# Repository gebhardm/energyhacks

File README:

energyhacks
===========

Some small gadgets providing certain convenience when doing energy metering,
consumption control, etc.

Project structure:
|
|--- AVRNetIOduino: Use the Pollin AVR NetIO board with the Arduino IDE
|
|--- Arduino: Miscellaneous sketches for the Arduino
|
|--- ElektroCamp: Slides of talks held at Elektro Camp events
|
|--- Impulsformer: Convert analog input from a current clamp to S0-impulses/kWh
|
|--- Netfrequency: Show the actual power grid frequency in a range of 50+/-0.2Hz
|
|--- OpticPulseSensor: Use a standard PLL schematics to optically detect pulses
|                      from gas or water meters
|
|--- Rapidbot: Software for the MakeMendel Rapidbot 3D printer V1.0 with
|              Generation6 driver board
|
|--- RaspberryPi: Some programs and scripts for use on a Raspberry Pi
|
|--- RS232-RS485-Converter: Convert legacy serial I/O to RS-485 with flow control 
|
`--- TempGuard: Use temperature sensors to control a warm water circulation pump

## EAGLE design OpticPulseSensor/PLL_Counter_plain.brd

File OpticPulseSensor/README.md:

#Optic Pulse Sensor

Use a NE567 to detect the reading of a reflexive optocoupler and drive the LED of an optocoupler
for galvanic decoupled open-collector output; the plain version is without the extra optocoupler
as the 567 has open collector (OC) output (in this case w/o galvanic decoupling).

Use the trimmer resistor to correctly detect light reflexion.

This schematics is set up corresponding to the many standard layouts to build a light barrier.
The frequency of the 567's oscillator is set to around 4 kHz, enough to prevent stray light
irritations.

Markus Gebhard, February 2013

Under MIT license.

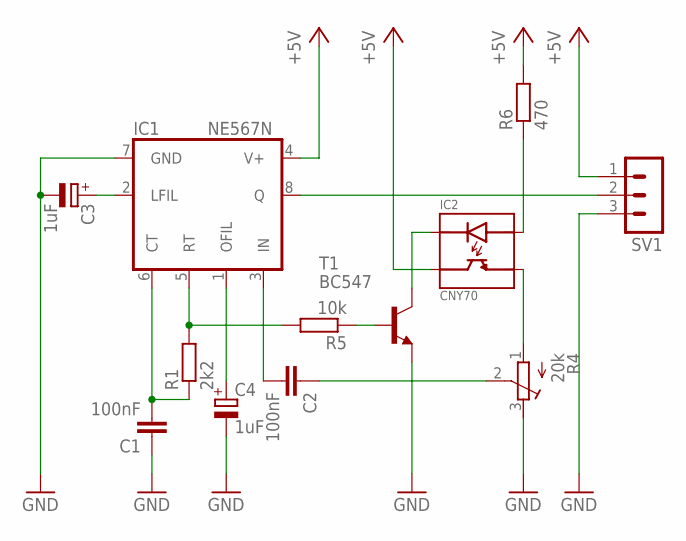
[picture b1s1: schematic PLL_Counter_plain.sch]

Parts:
C1, C2: 100nF; C025-025X050
C3, C4: 1uF; E2,5-5
IC1: NE567N; DIL08
IC2: CNY70
R1: 2k2; 0204/7
R4: 20k; RTRIM64X
R5: 10k; 0204/7
R6: 470; 0204/7
SV1: MA03-1
T1: BC547; TO92

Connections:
+5V: IC1.4 (V+), IC2.DC, R6.2, SV1.1
GND: C1.1, C3.-, C4.-, IC1.7 (GND), R4.3 (E), SV1.3, T1.1 (E)
unnamed: IC2.EK, T1.3 (C)
unnamed: IC1.5 (RT), R1.2, R5.2
unnamed: C1.2, IC1.6 (CT), R1.1
unnamed: IC1.8 (Q), SV1.2
unnamed: C2.2, IC1.3 (IN)
unnamed: IC2.DE, R4.1 (A)
unnamed: R5.1, T1.2 (B)
unnamed: IC2.EA, R6.1
unnamed: C3.+, IC1.2 (LFIL)
unnamed: C4.+, IC1.1 (OFIL)
unnamed: C2.1, R4.2 (S)

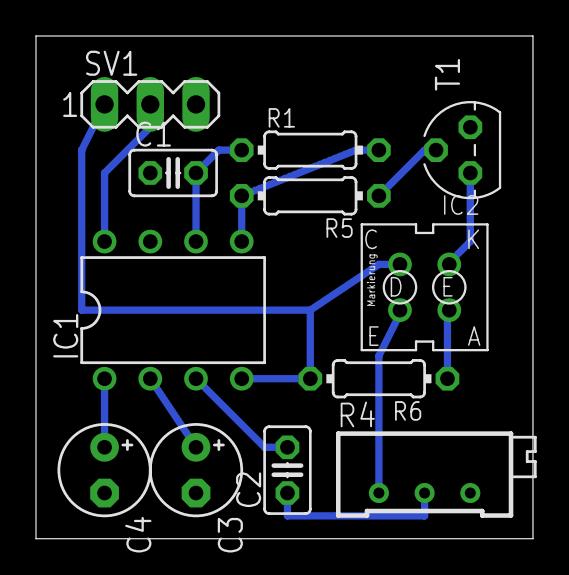
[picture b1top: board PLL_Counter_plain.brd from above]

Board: 2 copper layers, 27.6 x 27.9 mm, 12 parts (0 on the bottom side), 13 nets.

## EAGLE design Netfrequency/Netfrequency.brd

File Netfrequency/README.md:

# Measuring the mains frequency

This device shows with 9 LEDs the current frequency on which the grid
operates.

In Europe the mean grid frequency is 50Hz. Due to increasing
amount of renewable energy put into the grid it is said by the grid
administration "that it is hard to maintain the mean 50Hz". Thus by
too much power in the grid, the frequency rises (see the 50.2Hz problem
in the internet...)

This device - inspired by an Elektor article from January 2012 - allows
to check what is on the grid.
The current code indicates frequencies between 49,8Hz and 50,2Hz...

Have fun.

Markus Gebhard, Jan to July 2012

Needless to say: The grid's voltage may be harmful, so keep your fingers
off this device if you are not sure what you are doing ;-)

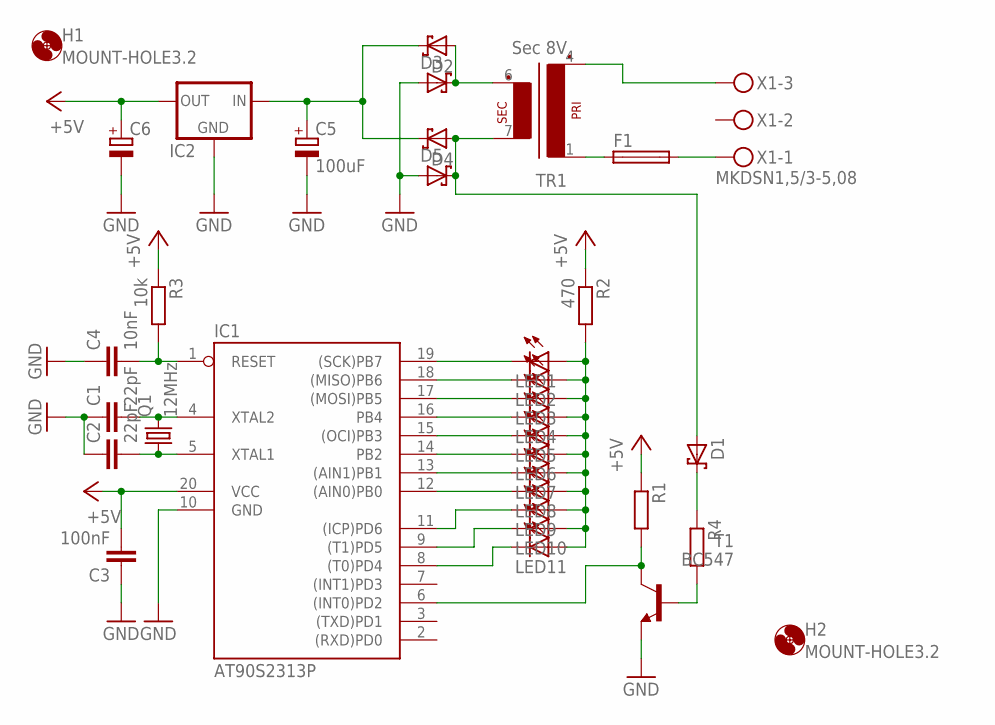
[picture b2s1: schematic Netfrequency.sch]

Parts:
C1, C2: 22pF; C025-025X050
C3: 100nF; C025-025X050
C4: 10nF; C025-025X050
C5: 100uF; E5-8,5
C6: CPOL-EUE2.5-6; E2,5-6
D1, D2, D3, D4, D5: SCHOTTKY-DIODEDO35-7; DO35-7
F1: SH22
H1, H2: MOUNT-HOLE3.2; 3,2
IC1: AT90S2313P; DIL20
IC2: 78LXX
LED1, LED2, LED3, LED4, LED5, LED6, LED7, LED8, LED9, LED10, LED11: LEDSQR2X5; LED2X5
Q1: 12MHz; HC49/S
R1, R4: R-EU_0204/7; 0204/7
R2: 470; 0204/7
R3: 10k; 0204/7
T1: BC547; TO92
TR1: Sec 8V; EE20-1
X1: MKDSN1,5/3-5,08

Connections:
+5V: C3.2, C6.+, IC1.20 (VCC), IC2.OUT, R1.1, R2.1, R3.1
GND: C1.1, C2.1, C3.1, C4.1, C5.-, C6.-, D3.A, D5.A, IC1.10 (GND), IC2.GND, T1.1 (E)
unnamed: IC1.19 ((SCK)PB7), LED1.K (C)
unnamed: IC1.18 ((MISO)PB6), LED2.K (C)
unnamed: IC1.17 ((MOSI)PB5), LED3.K (C)
unnamed: IC1.16 (PB4), LED4.K (C)
unnamed: IC1.15 ((OCI)PB3), LED5.K (C)
unnamed: IC1.14 (PB2), LED6.K (C)
unnamed: IC1.13 ((AIN1)PB1), LED7.K (C)
unnamed: IC1.12 ((AIN0)PB0), LED8.K (C)
unnamed: IC1.11 ((ICP)PD6), LED9.K (C)
unnamed: IC1.9 ((T1)PD5), LED10.K (C)
unnamed: IC1.8 ((T0)PD4), LED11.K (C)
unnamed: LED1.A, LED2.A, LED3.A, LED4.A, LED5.A, LED6.A, LED7.A, LED8.A, LED9.A, LED10.A, LED11.A, R2.2
unnamed: C1.2, IC1.4 (XTAL2), Q1.2
unnamed: C2.2, IC1.5 (XTAL1), Q1.1
unnamed: C4.2, IC1.1 (RESET), R3.2
unnamed: IC1.6 ((INT0)PD2), R1.2, T1.3 (C)
unnamed: D2.A, D3.C, TR1.6 (S3)
unnamed: C5.+, D2.C, D4.C, IC2.IN
unnamed: F1.1, TR1.1
unnamed: F1.2, X1.1
unnamed: TR1.4 (P2), X1.3
unnamed: R4.2, T1.2 (B)
unnamed: D1.C, R4.1
unnamed: D1.A, D4.A, D5.C, TR1.7 (S4)

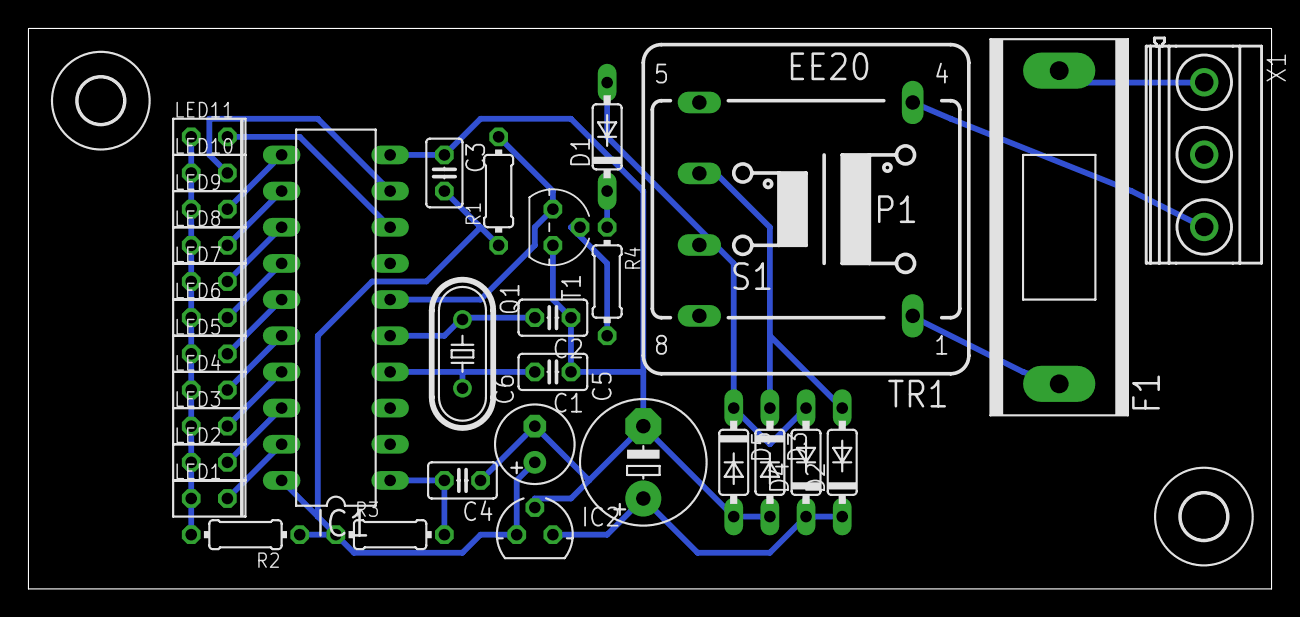
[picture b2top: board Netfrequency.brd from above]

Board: 2 copper layers, 87.3 x 39.4 mm, 35 parts (0 on the bottom side), 26 nets.

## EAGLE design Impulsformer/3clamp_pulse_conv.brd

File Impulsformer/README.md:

# Impulsformer
"Impulsformer" provides a little converter that transforms the current
measured by one respective three current clamp(s) (as used by the 
Fluksometer - see [flukso.net](www.flukso.net)) to an S0-compliant impulse set, 
in the example case 1000 impulses per measured kWh.

The basic use of the converter is for the Fluksometer to enhance it
by one (or three or more, as the used microcontroller's ADCs are not
fully utilized) analog input(s).

The given schematics, board and corresponding software are based on an
Atmel ATtiny13(A) and just a few external components.

The used voltage converter is a low drop variant capable to be "clamped"
to the existing Fluksometer's AC/DC module, so not requiring an
additional voltage source.

The microcontroller may be driven also with lower Vcc and different
operating frequency; the given outline of the one clamp variant is working fine...

Markus Gebhard, Karlsruhe, Germany, April/May 2012

Greetings to the participants of the electrocamp ec1205 held May 4th/5th in Offenburg.
It has been a pleasure taking part...

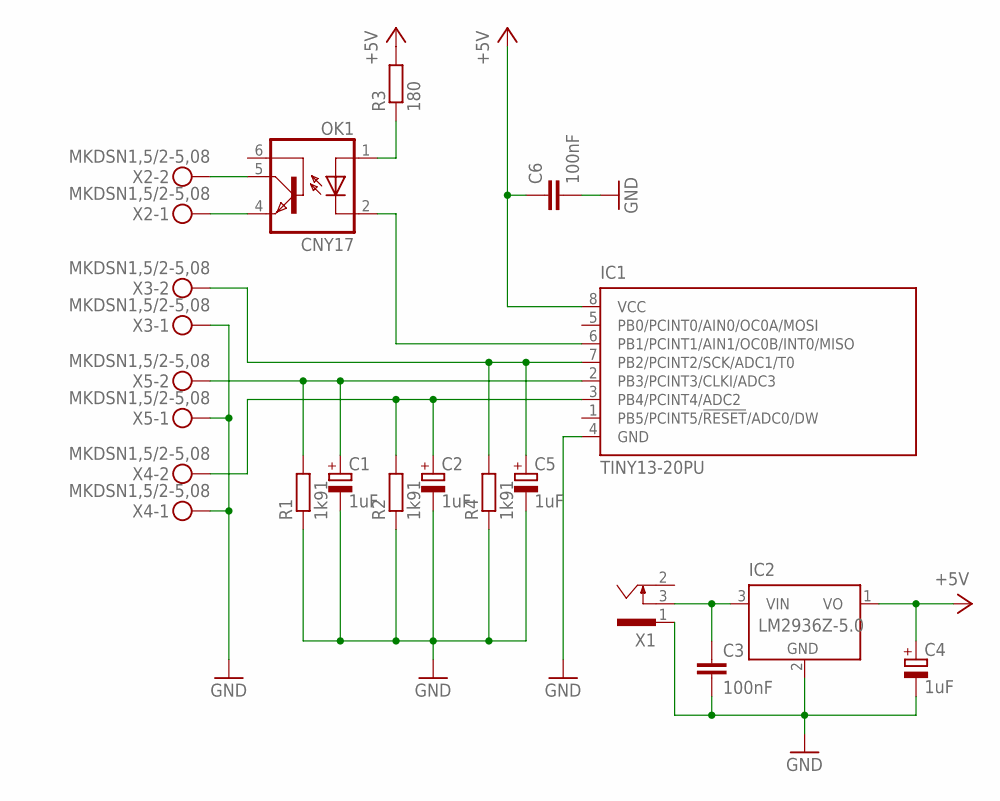
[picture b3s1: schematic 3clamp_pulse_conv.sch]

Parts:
C1, C2, C4, C5: 1uF; E2,5-5
C3, C6: 100nF; C025-025X050
IC1: TINY13-20PU; DIL08
IC2: LM2936Z-5.0; TO92
OK1: CNY17; DIL06
R1, R2, R4: 1k91; 0204/7
R3: 180; 0204/7
X1: SCD-014A; SCD-014-A
X2, X3, X4, X5: MKDSN1,5/2-5,08

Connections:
+5V: C4.+, C6.1, IC1.8 (VCC), IC2.1 (VO), R3.2
GND: C1.-, C2.-, C3.2, C4.-, C5.-, C6.2, IC1.4 (GND), IC2.2 (GND), R1.1, R2.1, R4.1, X1.1, X3.1, X4.1, X5.1
unnamed: C3.1, IC2.3 (VIN), X1.3
unnamed: C1.+, IC1.2 (PB3/PCINT3/CLKI/ADC3), R1.2, X5.2
unnamed: C2.+, IC1.3 (PB4/PCINT4/ADC2), R2.2, X4.2
unnamed: C5.+, IC1.7 (PB2/PCINT2/SCK/ADC1/T0), R4.2, X3.2
unnamed: OK1.1 (A), R3.1
unnamed: IC1.6 (PB1/PCINT1/AIN1/OC0B/INT0/MISO), OK1.2 (C)
unnamed: OK1.5 (COL), X2.2
unnamed: OK1.4 (EMI), X2.1

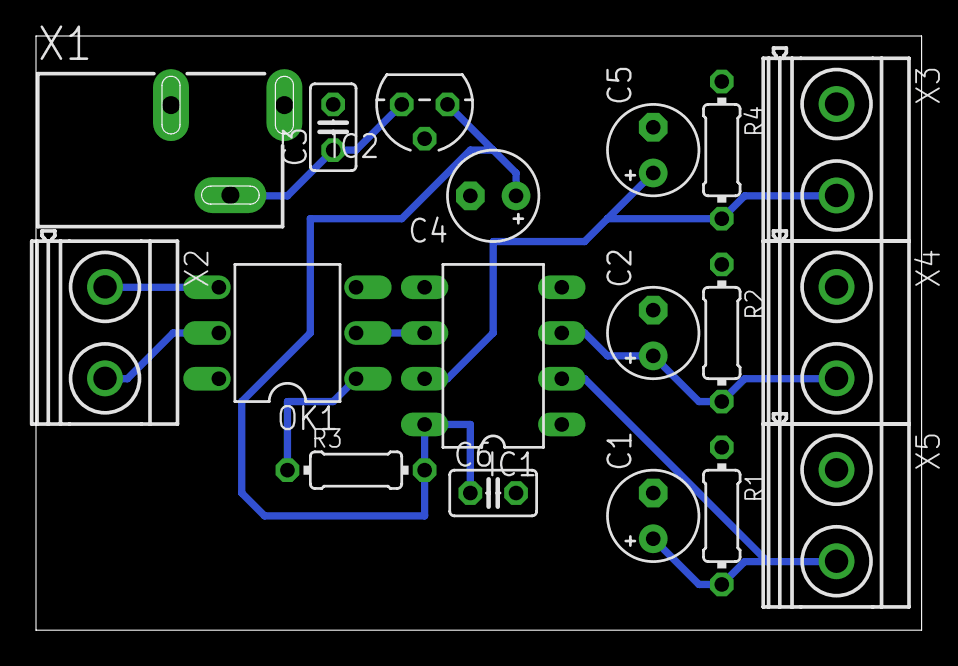
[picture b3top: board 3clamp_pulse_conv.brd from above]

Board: 2 copper layers, 49.2 x 33.0 mm, 18 parts (0 on the bottom side), 10 nets.

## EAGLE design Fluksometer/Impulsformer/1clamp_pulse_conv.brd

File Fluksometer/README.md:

# Fluksometer Additions

This folder contains stuff I made during my times of operating a
Fluksometer (FLM), a neat little appliance to do energy metering and display.

Refer to https://www.flukso.net/ for more details; the project seems abandoned.

As I also moved out of an environment where I could use the FLM "on premise",
this folder's content is mainly for the records and whomever wants to catch
up with some ideas spread in the respective community "that time".

* [FakeSensor](FakeSensor) - A simple fake sensor provider to test an MQTT broker
* [Flukso](Flukso) - Tips and tricks with respect to the flukso.net Fluksometer
* [Gauge](Gauge) - A simple Justgage gauge visualizing values received from MQTT topics
* [Graph](Graph) - A simple Flot graph visualizing values received from MQTT topics
* [Impulsformer](Impulsformer) - Convert analog input from a current clamp to S0-impulses/kWh
* [MQTTRealtime](MQTTRealtime) - A simple Chart graph visualizing values of an FLM03
* [OpticPulseSensor](OpticPulseSensor) - Use a standard PLL schematics to optically detect pulses from gas or water meters
* [RaspberryPi](RaspberryPi) - Some programs and scripts for use on a Raspberry Pi

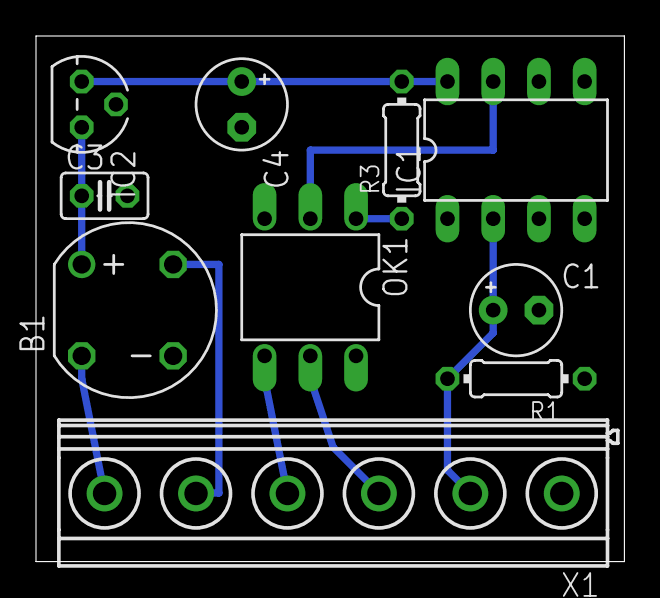
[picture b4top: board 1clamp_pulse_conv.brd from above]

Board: 2 copper layers, 32.7 x 29.2 mm, 10 parts (0 on the bottom side), 10 nets.

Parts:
B1: RB1A
C1: 1uF; E2,5-5
C3: 100nF; C025-025X050
C4: 10uF; E2,5-5
IC1: TINY13-20PU; DIL08
IC2: LM2936Z-5.0; TO92
OK1: CNY17; DIL06
R1: 1k91; 0204/7
R3: 150; 0204/7
X1: MKDSN1,5/6-5,08

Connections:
+5V: C4.+, IC1.8, IC2.1, R3.2
GND: B1.-, C1.-, C3.2, C4.-, IC1.4, IC2.2, R1.1, X1.1
unnamed: B1.+, C3.1, IC2.3
unnamed: C1.+, IC1.2, R1.2, X1.2
unnamed: IC1.7, OK1.2
unnamed: OK1.1, R3.1
unnamed: OK1.5, X1.3
unnamed: OK1.4, X1.4
unnamed: B1.AC2, X1.6
unnamed: B1.AC1, X1.5

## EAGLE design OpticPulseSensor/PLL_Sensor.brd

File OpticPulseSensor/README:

Optic Pulse Sensor

Use a NE567 to detect the reading of a reflexive optocoupler and drive the LED of an optocoupler
for galvanic decoupled open-collector output; the plain version is without the extra optocoupler
as the 567 has OC output (in this case w/o galvanic decoupling).

Use the trimmer resistor to correctly detect light reflexion.

This schematics is set up corresponding to the many standard layouts to build a light barrier.
The frequency of the 567's oscillator is set to around 4 kHz, enough to prevent stray light
irritations.

Markus Gebhard, February 2013

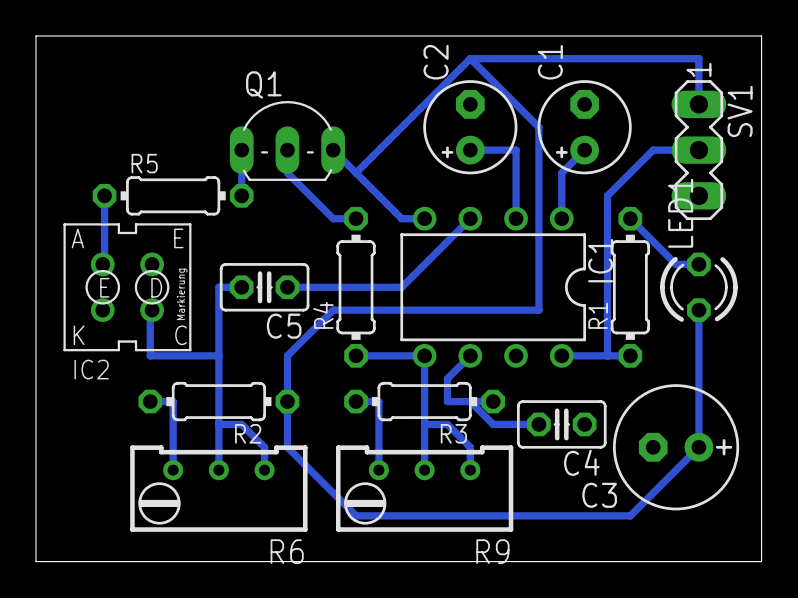
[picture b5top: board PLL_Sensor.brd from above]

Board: 2 copper layers, 40.3 x 29.2 mm, 17 parts (0 on the bottom side), 15 nets.

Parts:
C1, C2: 1uF; E2,5-5
C3: 100uF; E2,5-7
C4: 33nF; C025-025X050
C5: 100nF; C025-025X050
IC1: LM567N; DIL08
IC2: CNY70
LED1: LED3MM
Q1: BC558B; TO92-EBC
R1: 1k; 0204/7
R2, R3: 4k7; 0204/7
R4, R5: 0204/7
R6, R9: 10k; RTRIM64W
SV1: MA03-1

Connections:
+5V: C3.+, IC1.4, LED1.A, Q1.E, R2.1, SV1.1
GND: C1.-, C2.-, C3.-, C4.1, IC1.7, IC2.DE, IC2.EK, SV1.3
unnamed: IC1.8, R1.1, SV1.2
unnamed: LED1.K, R1.2
unnamed: C2.+, IC1.2
unnamed: C1.+, IC1.1
unnamed: C5.1, IC1.3
unnamed: C5.2, IC2.DC, R6.1, R6.2
unnamed: Q1.C, R5.2
unnamed: R2.2, R6.3
unnamed: IC2.EA, R5.1
unnamed: Q1.B, R4.2
unnamed: IC1.5, R4.1, R9.1, R9.2
unnamed: R3.2, R9.3
unnamed: C4.2, IC1.6, R3.1

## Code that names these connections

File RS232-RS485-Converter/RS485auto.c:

/**********************************************************************
Use an ATtiny 13 to drive the write enable pin of a MAX485 to pass
RS-232 characters for the time of a character write

Used to test the RS-485 interface of an SMA DC converter

Markus Gebhard, Karlsruhe, Copyright 2009

This program is free software: you can redistribute it and/or modify
it under the terms of the GNU General Public License as published by
the Free Software Foundation, either version 3 of the License, or
(at your option) any later version.

This program is distributed in the hope that it will be useful,
but WITHOUT ANY WARRANTY; without even the implied warranty of
MERCHANTABILITY or FITNESS FOR A PARTICULAR PURPOSE.  See the
GNU General Public License for more details.

You should have received a copy of the GNU General Public License
along with this program.  If not, see <http://www.gnu.org/licenses/>.
**********************************************************************/

#include <avr/io.h>
#include <avr/interrupt.h>
#include <util/delay.h>

int main()
{
	unsigned char jmprs = 0;
	// init ATtiny13
	// PB0 - RSwrite Output
	// PB1/INT0 - Activity on RS232-TxD-line
	// PB2, 3, 4 - Jumper for Baudrate
	// PB5 unused due to being reset line
	// set PB0 output, all others input
	DDRB |= (1<<PB0);
	// internal Pullup resistors on
	PORTB |= (1<<PB1)|(1<<PB2)|(1<<PB3)|(1<<PB4);
	// /RE on MAX485 to low => read
	PORTB &= ~(1<<PB0);
	// read jumpers for baud setting
	jmprs |= (PINB>>2)&7;
	// main loop to react on RS-232 write
	while (1)
	{
		if (!(PINB&(1<<PB1)))
		{
			PORTB |= (1<<PB0);
			// delay until a character is sent - with some correction
			if 		(jmprs==7)	_delay_us(86);		// 115k2 baud
			else if (jmprs==6)	_delay_us(173-1);	// 57k6
			else if (jmprs==5)	_delay_us(260-2);	// 38k4
			else if (jmprs==4)	_delay_us(520-2);	// 19k2
			else if (jmprs==3)	_delay_us(1041-3);	// 9k6
			else if (jmprs==2)	_delay_us(2083-3);	// 4k8
			else if (jmprs==1)	_delay_us(4166-4);	// 2k4
			else 				_delay_us(8333-5);	// 1k2
			PORTB &= ~(1<<PB0);
		}
	}
	// und tschüß...
	return (0);
}

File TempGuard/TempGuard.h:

/* TempGuard.h version 4.0 */

#include <avr/io.h>
#include <avr/interrupt.h>
#include <util/delay.h>

#define SW_DDR DDRB				// direction of switch port
#define SW_PORT PORTB			// port of switches
#define SW_PIN PINB				// read set switches
#define PUMP PB1				// pin of pump switch

#define BUT_DDR	DDRB			// direction of button port
#define BUT_PORT PORTB			// port of buttons
#define BUT_PIN PINB			// read buttons
#define PLUS PB5				// (+)-button
#define ENTER PB4				// enter button
#define MINUS PB3				// (-)-button

#define RUNTIME 300				// maximum runtime of pump in seconds
#define DT_ON 10				// pump on at 10 Kelvin difference
#define DT_OFF 5				// pump off at 5 Kelvin difference
#define DT_MAX 10				// difference to maximum temperature at pump off
#define WW_MIN 40				// minimal temperature of warm water to start
#define CI_MAX 30				// maximum temperature of circulation
#define T_DOWN 15				// temperature lower limit
#define T_UP 95					// temperature upper limit
#define TCLOCK 206				// Timer start 50Hz: Second >> 256-50
#define SMPL 5					// Sampling all SMPL seconds

#define LCD_DDR	DDRD			// direction of LCD port
#define LCD_PORT PORTD			// port of LCD
#define LCD_PIN PIND			// read LCD port
#define LCD_CLK PD6				// clock-pin of shift register
#define LCD_DATA PD5			// data-pin of shift register
#define LCD_LIGHT PD7			// background light
#define RS_CMD 0				// send command to LCD
#define RS_DATA 1				// send data to LCD
#define LIGHT 60				// time background light on
// Menu definition
#define MENU_TEMP 1
#define MENU_DTON 2
#define MENU_DTOFF 3
//#define MENU_CLOCK 4
#define MENU_CMAX 4
#define MENU_CMIN 5
#define MENU_RESET 6
#define MENU_TMAX 7
//#define MENU_DTMAX 9
#define MENU_MAN 8				// number of menus; last one is always "manual control"

volatile unsigned char SampleCnt;		// counter to next sampling
volatile int T_Ww, T_Ci;				// measured temperatures of warm water and circulation
volatile int T_max;						// measured maximum temperature
volatile int T_last;					// last measured temperature
volatile int dT_on = DT_ON;				// DeltaTemp of pump on
volatile int dT_off = DT_OFF;			// DeltaTemp of pump off
volatile int dT_max = DT_MAX;			// DeltaTemp to MaxTemp of pump off
volatile int T_Ci_max = CI_MAX;			// maximum temperature of circulation
volatile int T_Ww_min = WW_MIN;			// minimum temperature of circulation
volatile unsigned int Rnt = 0;			// runtime of pump
volatile unsigned int t_run = RUNTIME;  // maximum runtime of pump
volatile unsigned char Bkl = 0;			// runtime background light
volatile struct time_struct {
	unsigned char Hrs:5;
	unsigned char Min:6;
	unsigned char Sec:6;
} Time;

volatile unsigned char Hrs, Min, Sec, Day, Mnt, Yr, Menu;

void init_ADC( void );
int read_ADC( unsigned char );
void init_switch( void );
void init_button( void );
void init_TIMER( void );
void Switch_pump( char );
void Switch_light( char );
void User( void );
void Control_pump( void );

void LCD_clock( void );
void LCD_write_nibble(unsigned char, unsigned char );
void LCD_write(unsigned char, unsigned char );
void LCD_clear( void );
void LCD_home( void );
void LCD_init( void );
void LCD_text( char* );
void LCD_pos( unsigned char, unsigned char );
void LCD_int( int );

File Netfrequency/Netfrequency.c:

/* Application to display the net frequency with 9 LEDs
on a ATtiny2313 running at 12MHz
(instead of an AT89C2051P as in German Elektor 01-2012,
pages 22 and following)
INT0 is used to couple the net frequency
LEDs on PORTB: PB7-0 and PORTD: PD6
red:  PB7
yellow: PB6,5
green: PB4,3,2
yellow: PB1,0
red:  PD6

This program is free software: you can redistribute it and/or modify
it under the terms of the GNU General Public License as published by
the Free Software Foundation, either version 3 of the License, or
(at your option) any later version.

This program is distributed in the hope that it will be useful,
but WITHOUT ANY WARRANTY; without even the implied warranty of
MERCHANTABILITY or FITNESS FOR A PARTICULAR PURPOSE.  See the
GNU General Public License for more details.

You should have received a copy of the GNU General Public License
along with this program.  If not, see <http://www.gnu.org/licenses/>.
*/
/***************************************************************************/
//used standard includes 
#include <stdlib.h>
#include <avr/io.h>
#include <avr/interrupt.h>
#include <util/delay.h>
/***************************************************************************/
#define AVG	  				// measure frequency with average calculation
//#define RS232
#ifdef RS232
#define BAUD 19200              // RS232 speed for debugging purposes
#endif
#define NET 50					// set Net default frequency
#define DIVIDER 8				// Prescaler of Timers
#define NETCNT (unsigned int) (F_CPU / DIVIDER / NET) // relevant count takts per Hz
#define DELTA 30				// delta counts per LED
// define the LEDs display frequencies
// example for 50Hz as in Europe:
// Factor = 12.000.000 / 8 / 50 = 30.000 counts equal 50 Hz
// Limits in Europe are 50,2 Hz and 49,8Hz
// 50,2Hz equal 30.120 counts, 49,8Hz equal 29.880 counts
// distributed on 9 LEDs with 50Hz in the center give a delta per LED of 30 counts
/***************************************************************************/
//Header Definition of used  routines (I don't like header files :-))
#ifdef RS232
void init_USART( unsigned int );
void send_USART( unsigned char );
void sendchars_USART( char* );
void send_uint( unsigned int );
#endif
void LED_init( void );
void LED_set( unsigned char );
void LED_clr( unsigned char );
void LED_off( void );
void LED_toggle( unsigned char );
/***************************************************************************/
//Global variables for Interrupt computation
volatile unsigned char lastLED = 0;
volatile unsigned long sum = 0;
volatile unsigned char cnt = 0;
/***************************************************************************/
//Interrupt Routines for computing INT0
ISR(INT0_vect)
{
	int led, timer, t_Hz;
	timer = TCNT1;
	TCNT1 = 0;
	t_Hz = F_CPU / DIVIDER / timer;
	// use timer value only if variance not too large (there are false counts)
	if (abs(NET-t_Hz)<5)
	{
		// measure with average calculation over last second
#ifdef AVG
		sum += timer;
		cnt++;
		if (cnt == NET)
		{
			// the average
			sum /= NET;
			// mapped onto the LEDs
			led = sum;
			led -= NETCNT;
			led /= DELTA;
			led += 5;
			LED_clr(lastLED);
			LED_set(led);
			lastLED = led;
			sum = 0;
			cnt = 0;
		}
#else
		// output measured value directly
		led = timer;
		led -= NETCNT;
		led /= DELTA;
		led += 5;
		LED_clr(lastLED);
		LED_set(led);
		lastLED = led;
#endif
	}
}
/* check, if Timer overflows
ISR(TIMER1_OVF_vect)
{
	TCNT1 = 0;
} */
/***************************************************************************/
#ifdef RS232
//RS-232 Routines
void init_USART( unsigned int bps )
{
	unsigned int baud;
	baud = ( F_CPU / 16UL / bps ) - 1;       // compute Teiler
	UBRRH = (unsigned char) (baud>>8);       // set Baudrate
	UBRRL = (unsigned char) baud;
	UCSRB = (1<<RXEN)|(1<<TXEN);             // RS232-Rx/Tx on
	UCSRC = (3<<UCSZ0);                      // set Protocol 8N1
}

void send_USART( unsigned char c )
{
	while ( !( UCSRA & (1<<UDRE)) );  // wait until transfer buffer empty
	UDR = c;                          // write char
}

void sendchars_USART( char *s )
{
	while ((*s != 0))
	{                                 // output all chars
		send_USART(*s++);
	} 
}

void send_uint( unsigned int n )
{
	unsigned char dig[5], num = 0, i; // compute 5 digit integer without sign
	do
	{
		dig[num++] = ( n % 10 ) + 0x30;
		n /= 10;
	} while (n != 0);
	for (i=num; i!=0; i--) send_USART(dig[i-1]);
}
#endif
/***************************************************************************/
// LED Routines
void LED_init( void )
{
	DDRB = 0xff;
	DDRD = (1<<PD6);
	PORTB = 0xff;
	PORTD = (1<<PD6);
}
// LED on
void LED_set( unsigned char n )
{
	if ((n>0) && (n<9)) PORTB &= ~(1<<(8-n));
	else if (n==9) PORTD &= ~(1<<PD6);
}
// LED off
void LED_clr( unsigned char n )
{
	if ((n>0)&&(n<9)) PORTB |= (1<<(8-n));
	else if (n==9) PORTD |= (1<<PD6);
}
void LED_off( void )
{
	PORTB = 0xff; PORTD = (1<<PD6);
}
void LED_toggle( unsigned char n )
{
	if (n<9) PORTB ^= (1<<(8-n));
	else if (n==9) PORTD ^= (1<<PD6);
}
/***************************************************************************/
// main program
int main( void )
{
	unsigned char i; 		     // counter variable
	// Ausgabe vorbereiten
#ifdef RS232
	init_USART( BAUD );
	send_USART(27); sendchars_USART("[2J"); // clear screen
	sendchars_USART("Net loupe");
#endif
	// Net frequency read preparation
	//MCUCR |= (0x02 << ISC00);  // Interrupt on falling edge of INT0
	MCUCR |= (0x03 << ISC00);  // Interrupt on rising edge on INT0
	GIMSK |= (1 << INT0);   	 // release INT0
	// Timer initialization
	switch (DIVIDER)
	{
	case 1: TCCR1B |= (0x01 << CS10); break; 
	case 8: TCCR1B |= (0x02 << CS10); break; 
	case 64: TCCR1B |= (0x03 << CS10); break;
	}
	//TIMSK  |= (1 << TOIE1);  // Interrupt on timer overflow
	// LEDs initialization
	LED_init();
	// LEDs count through (used just as a appetizer)
	for (i=1;i<=9;i++)
	{
		LED_set(i);
		_delay_ms(250);
		LED_clr(i);
	}
	// Frequency measuring preparation
	sei();                    // activate Interrupt control
	TCNT1 = 0;         		// Timer start
	// program main loop - everything is done in the interrupt
	while (1)
	{
	}
	return(0);
}

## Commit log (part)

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2012-04-20 Initial commit of the source code, schematics and board layout of an analog current clamp to S0 converter. Idea is to add "at least" two more analog channels to the Fluksometer by converting analog t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
2012-04-27 Adding a brief description of the hack
2012-04-28 Add temperature control project
2012-05-06 Adapted code and schema to 1 and 3 clamp variants
2012-05-06 Readme update
2012-05-06 Use plain text for README
2012-05-12 Corrections (result of thinking w/o compiling)
2012-05-13 RS485/RS232 Converter added
2012-05-13 RS485/RS232 jpg and README upd
2012-05-17 Moved to interrupt due timing issues
2012-05-18 Timing is strange...
2012-07-01 Small correction of modulo calculation
2012-07-08 Netfrequency observer added
2012-08-20 Simplicity is not always obvious...
2012-08-21 timing adaptation
2012-08-25 filtering timer measurements
2012-11-11 Start to use Pollin AVR NetIO with Arduino
2012-11-12 Added AVR NetIO Arduino bootloader for ATmega32
2012-11-15 Working Arduino bootloaders for AVR NetIO w/ ATmega644P and 32
2012-11-16 Description update
2012-11-19 Preparation for correct AVRNetIOduino hardware files
2012-11-19 Correct description
2012-12-15 Bootloader LED on prog select jumper
2013-01-12 AVRNetIO minimal server running
2013-01-13 AVRNetIO working with mega32 and mega644p
2013-02-03 TempGuard on Arduino
2013-02-03 TempGuard simple Web display
2013-02-23 Optical Sensor added
2013-02-23 readme upd
2013-02-28 Optoreader with accuracy trimming
2013-03-17 AVRNetIOduino revisited
2013-04-21 ElektroCamp slides
2013-04-21 ReadMe updates
2013-04-26 elektro:camp slides revised
2013-05-11 read Fluksometer with Raspberry Pi
2013-05-11 FLM sensor reader corrected
2013-05-11 readme files updated
2013-05-12 Sensor ID from GUID to str
2013-05-13 logging added
2013-05-13 error handling cont'd
2013-05-14 error enumeration!
2013-05-14 bracket or no bracket, that is the question
2013-05-15 error handling update
2013-05-16 version for mid-time test
2013-05-17 testing and error correction, next round
2013-05-19 small adjustment
2013-05-23 job end handler added
2013-05-24 something learned:funcdef before call
2013-05-30 some more error handling
2013-06-02 first experiences with flot
2013-06-03 flm data visualization cont'd
2013-06-03 there is always a typo...
2013-06-03 timestamp visualization corrected
2013-06-15 Readme on FLM to db scripts
2013-07-10 return from manual mode after max runtime
2013-07-13 translation to English
2013-07-14 translation to English finished
2013-07-14 pump manual runtime
2013-07-17 manual handling corrected
2013-07-20 minor correction on return from manual
2013-08-31 clean-up and reduction to the needed
2013-09-08 Minor corrections/correct schematics
2013-09-21 Include 3D printer config
2013-09-29 FLM MQTT to DBscript added
2013-09-30 Comments and reconnect-loop added
2013-09-30 Minor corrections
2013-12-23 Arduino sketches added
2013-12-23 100kW Offset added
2013-12-23 Tiny corrections and osciloscope picture
2013-12-27 Offset as define; debug extended
2013-12-27 Delete Thumbs.db
    No comment on this crap...
2013-12-27 Display energy on define
2014-01-17 HowTo to use mySQL and python to store FLM data
2014-01-18 Explanation extended by further findings
2014-02-02 FLM MQTT panel draft added
2014-02-03 Automatic sensor detection
2014-02-03 ReadMe added
2014-02-03 Time of message added to gauge
2014-02-05 Sparkline graph added
2014-02-06 clean up and restructuring
2014-02-06 screenshot added
2014-02-06 FLM mqtt panel works in any node environment
2014-02-07 host IP retrieval w/o manually setting
2014-02-08 License added
2014-02-09 http and io on same port
2014-02-14 Tiny modification on server determination
2014-02-15 dynamic sensor to table assignment
2014-03-01 AVRNetIO as simple MQTT publisher
2014-03-01 allow topic to just contain value, no array
2014-03-07 payload extended
2014-03-08 provide JSON payload
2014-03-08 independent gauge updates
2014-03-20 panel with counters
2014-03-21 gauge counting
2014-03-22 counters separated
2014-03-29 measure net frequency
2014-03-29 comments added
2014-03-29 README
2014-04-12 'configure' added
2014-04-26 mySQL prep
2014-04-27 generic sensor storage
2014-04-27 Cleanup
2014-04-29 Clean up of ATmega32 pins
2014-04-29 insertion cleanup
2014-05-01 persistence via .js
2014-05-02 start scrript added
2014-05-03 jquery/bootstrap update
2014-05-03 file authorizations
2014-05-03 prepare serving chart
2014-05-04 Netfrequency experiment
2014-05-06 charting experiment cont'd
2014-05-10 getting db values
2014-05-10 take a break
2014-05-10 flot.time added
2014-05-11 working chart
2014-05-15 correct time axis, labels
2014-05-15 dynamic plot width
2014-05-17 script part decoupled
2014-05-17 selectable time interval added
2014-05-18 alternative chart display
2014-05-19 think fingers
2014-05-24 database access on demand
2014-05-29 beautifying
2014-05-30 using bootstrap grid
2014-05-30 screeshots renewed
2014-06-02 index added
2014-06-09 average handling added
2014-06-13 small corrections after feedback
2014-06-13 adding the lost '
2014-06-14 panel adapted to new version of socket.io
2014-06-14 panel_new starter added
2014-06-14 version cleanup
2014-06-29 German papers added
2014-08-02 Flukso tips and tricks
2014-08-31 AVRNetIOduino to send DS18S20 temperatures via MQTT
2014-08-31 AVRNetIOduino docu revised
2014-08-31 links corrected
2014-09-06 LED flashes to show activity
2014-09-18 temperature publishing also with original Arduino Ethernet
2014-09-20 some further testing
2014-10-13 ReadMes updated
2014-10-13 Uppercase?
2014-10-15 Update due to Github's pickiness on file extensions
2014-10-15 Upd file extension in links
2014-10-16 another round updating readmes
2014-10-25 sensing and publishing DHT11 readings
2014-10-25 Correct link to flmdisplay
2014-10-25 Links consist of text AND link ;-)
2014-10-25 DHT lib added w/ Celsius heat index
2014-10-25 cleanup corrupted lib folder
2014-10-25 repair Arduino DHT lib
2014-11-01 yet another clean-up
2014-11-13 brief intro to IoT
2014-12-06 FLM local visualization
2014-12-06 reconnect/JPMens
2014-12-06 move of FLMlocal to own repo
2015-01-09 minimalistic gauges added (strip from flmdisplay)
2015-01-09 ReadMe revised
2015-04-04 added MQTT graph display
2015-04-04 gauge to new mqtt handling
2015-04-08 Log MQTT connection only when connected
    Some more connection and error handling to be added...
2015-04-08 formatting
2015-04-09 adapt to new mqtt payload format
2015-04-10 Get Gauge running on a windows PC
    Adaptations to current mqtt and socket.io modules; following installation steps performed:
    Install node.js v0.12.2
    npm install mqtt socket.io (be aware to have python installed)
    Install mosquitto 1.4.1 (incl. pthreads-2.9.1, OpenSSL, vc 2008 redist)
    run node serve_mqtt.js
    run mosquitto -v (to see traffic)
2015-04-10 add package.json
2015-04-11 synchronizing gauge and graph
2015-04-11 graph to serve graph.html
2015-04-11 Clear typos
2015-04-15 justgage update
2015-04-26 prepare for Arduino 1.6.x
2015-04-27 make compatible with IDE 1.6.x cont'd
2015-08-19 mdns enablement and package update
2015-08-22 test FLM stuff on desktop
2015-08-22 picture and broker tweak
2015-11-21 Arduino experiments
2015-11-23 Added some comments
2015-11-29 description revised
2015-12-11 Pin Layout reformatted
2015-12-23 uÃpdate to 1.6.9 variant
2015-12-23 update to AVRNetIO docu
2016-01-21 add error handling - mdns currently not working
2016-01-24 resolve mdns issue
2016-01-24 update to working conditions
2016-03-06 FLM hacks moved
2016-04-12 slides for grid:camp
2016-04-16 provide a fake sensor MQTT publisher
2016-05-16 Bootloader for ENC clocked ATmega
2016-06-05 first steps in KiCAD
2016-07-28 gauges work with FLM03
2016-07-31 package update
2016-07-31 graph works with FLM03 - but very slowly
2016-08-07 adapt decimals
2016-08-20 helper to understand FLM03 measuring
2016-08-20 sample analysis
2016-08-20 set fixed y axis
2016-08-20 gain more stability
2016-08-30 try bootstrap - not satisfactory
2016-08-31 add toggle between current and voltage
2016-09-17 switch to bootstrap 2 - IMHO nicer
2016-09-17 behaviour same as in flm03
2016-09-18 make combined chart alternative
2016-09-19 refresh chart on selection change
2016-09-24 try out chart refresh
2016-09-29 I still do not understand why there is no initial chart
2016-09-30 update dependencies
2016-10-03 script to detect external IP address
2016-10-03 more experiments with connection
2016-10-04 simple net frequency publishing
2016-10-04 fix typos, as usual ;-)
2016-10-04 make working experimental version
2016-10-08 elektro:camp 2016.10
2016-11-01 start to dig into rfm01 handling
2016-11-01 get it compiling :-)
2016-11-01 add receiving method
2016-11-01 reflect command bits
2016-11-02 I feel it is not right yet...
2016-12-18 cont'd experiment to transmit the net frequency
2016-12-24 further experimenting with mains frequency measurement
2016-12-28 grrr, int division is a mess
2016-12-28 experimenting with no prescaling
2017-01-05 how weird is Arduino IRQ handling?!
2017-01-08 enable raspi to send external ip address by mail
2017-10-02 Stupid markown incompatibility
2017-10-02 Stupid markdown incompatibility
2017-10-02 quick and dirty MQTT publisher
2017-10-08 publish temperatur to an FLM
2018-05-19 Using another kind of frequency measurement
2019-03-12 Minor correction of formatting
2019-07-21 start of HP03S experiment; not complete yet
2019-07-24 Include MQTT publishing
2019-07-27 Extend by BME280 environment sensor
2019-08-08 Add MIT license as the most likely to adhere
2019-08-28 A sunday afternoon project
2019-08-28 Add exemplary implementation
2019-12-03 move MAX7219 lib to Arduino section as incomplete
2019-12-03 add bitbang sources
2020-02-20 correct link to gauge display
2020-04-19 cleanup and Game of Life
2020-04-19 Add info on GoL
2020-04-20 Add picture of Game of Life setup
2020-04-21 Some optimizations
2020-04-22 Add picture of Game of Life implementation
2020-04-23 add GoL with NeoPixels
2020-04-25 Update mail send option
2020-04-30 old jquery version deleted due to vulnerability
2020-04-30 jquery link replaced due to vulnerability
2020-04-30 jquery.js deleted due to vulnerability
2020-04-30 jquery replaced due to vulnerability
2021-12-01 neighborhood calculation revised
2021-12-02 get compare right :-/
2021-12-04 clean up
2023-09-10 Game of Life for IKEA Obegränsad
2023-09-11 Use standard variable types and some comments
2023-09-17 comments and initialization
2023-09-18 showing an Apfelmännchen on a 8x8 Neopixel matrix
2023-09-18 Mandelbrot Set example
2023-09-18 Update README.md w/ Mandelbrot Set
2023-09-23 lookup table replaced by code
2023-09-24 Clean up FLM stuff
2023-09-24 Further cleanup
2023-09-25 variables
2023-12-26 Add GoL for IKEA Frekvens LED cube
2023-12-31 Change to SPI data transfer and correct LED mapping
2024-01-06 Weather display on IKEA Obegraensad LED lamp
2024-01-09 adapt environment display, allow numbers
2024-01-10 renew sun and clouds
2024-01-11 handle pressure display
2024-01-14 cloud shift
2024-02-28 make % prettier
2024-03-17 revision colored GoL
2024-03-28 add fade effect
2024-03-28 memory irritation
2024-03-28 a second fade effect
2024-03-30 some clean-ups
2024-03-30 add Game of Life
2024-04-28 README.md aktualisieren
2025-03-23 Update Envi_Obegraensad.ino w/o buttons, w/ fade
